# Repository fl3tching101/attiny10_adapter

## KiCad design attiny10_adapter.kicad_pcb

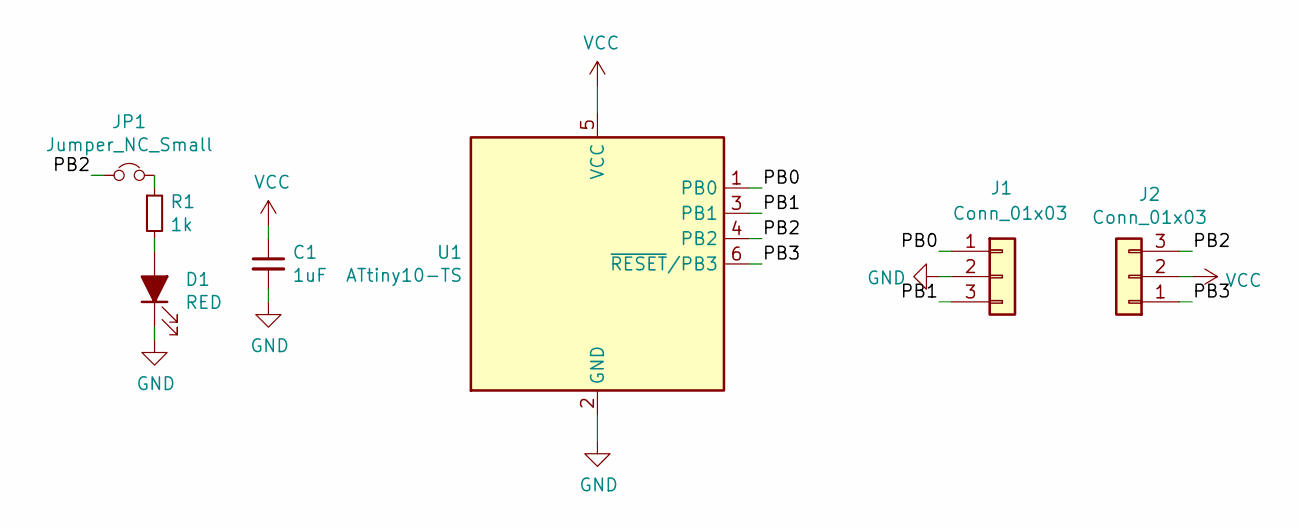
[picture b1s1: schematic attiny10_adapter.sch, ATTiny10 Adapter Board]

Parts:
C1: 1uF; C_0603_1608Metric
D1: RED; LED_0603_1608Metric
J1, J2: Conn_01x03; PinHeader_1x03_P2.54mm_Vertical
JP1: Jumper_NC_Small; SolderJumper-2_P1.3mm_Bridged_Pad1.0x1.5mm
R1: 1k; R_0402_1005Metric
U1: ATtiny10-TS; SOT-23-6

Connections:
/PB0: J1.1, U1.1 (PB0)
/PB1: J1.3, U1.3 (PB1)
/PB2: J2.3, JP1.1, U1.4 (PB2)
/PB3: J2.1, U1.6 (~RESET~/PB3)
GND: C1.2, D1.1 (K), J1.2, U1.2 (GND)
unnamed: D1.2 (A), R1.2
unnamed: JP1.2, R1.1
VCC: C1.1, J2.2, U1.5 (VCC)

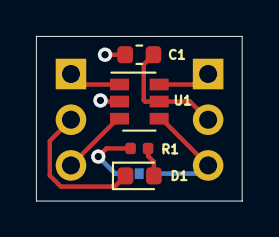
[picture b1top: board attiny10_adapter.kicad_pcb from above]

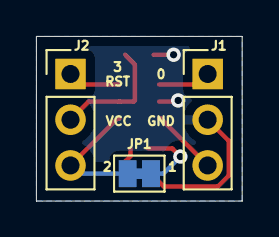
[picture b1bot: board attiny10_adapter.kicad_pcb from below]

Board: 2 copper layers, 11.4 x 9.1 mm, 7 parts (3 on the bottom side), 8 nets.

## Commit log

2021-12-30 Initial commit - used for Osh Park order
